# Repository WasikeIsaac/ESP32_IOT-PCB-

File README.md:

# ESP32_IOT-PCB-
ESP32 IoT board: 4-layer KiCad PCB with USB-C, BME280, mic, audio amp, SD card, GPIO breakout. Full custom design from schematic to layout.

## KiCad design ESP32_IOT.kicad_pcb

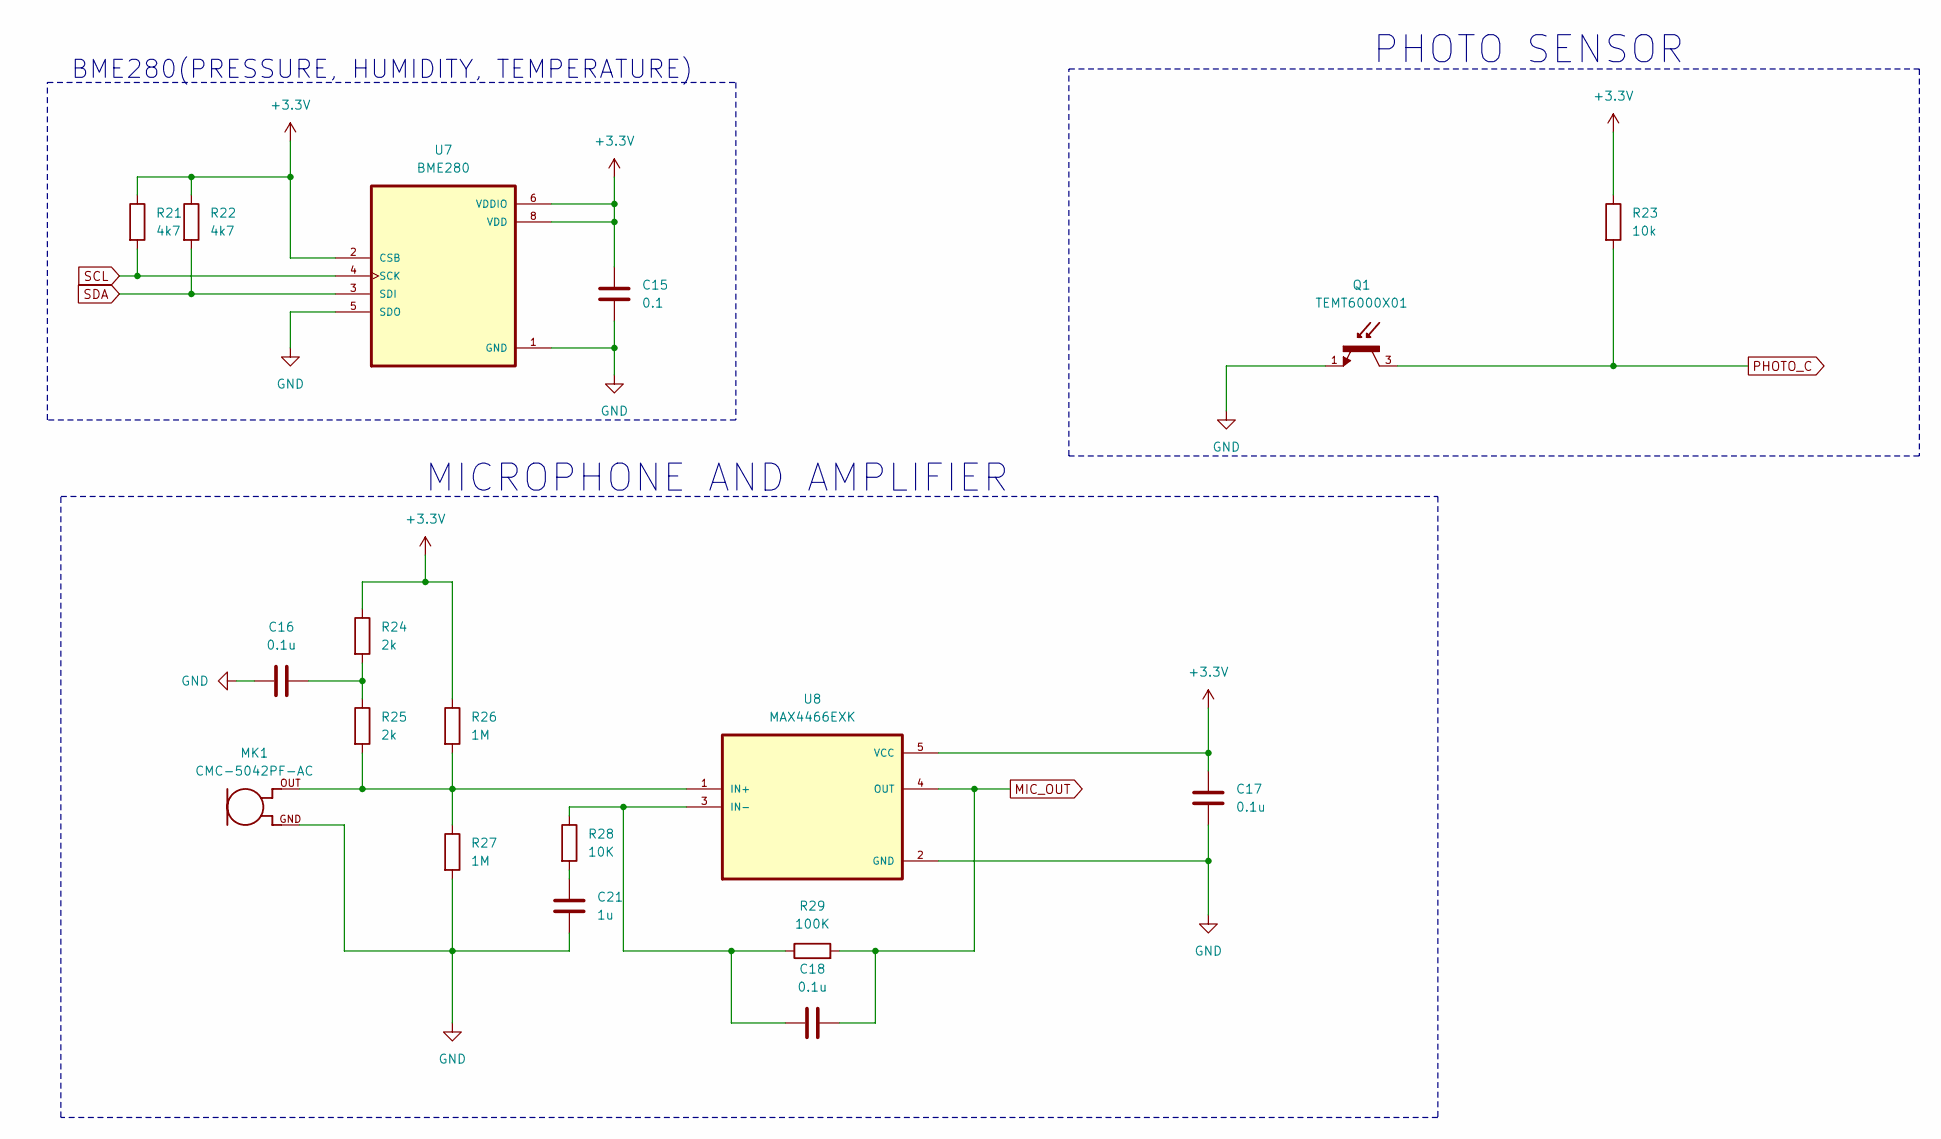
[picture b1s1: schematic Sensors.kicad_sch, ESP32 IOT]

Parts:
C15: 0.1; C_0805_2012Metric
C16, C17, C18: 0.1u; C_0805_2012Metric
C21: 1u; C_0805_2012Metric
MK1: CMC-5042PF-AC; CUI_CMC-5042PF-AC
Q1: TEMT6000X01; TRANS_TEMT6000X01; PARTREV 1.9
R21, R22: 4k7; R_0805_2012Metric
R23: 10k; R_0805_2012Metric
R24, R25: 2k; R_0805_2012Metric
R26, R27: 1M; R_0805_2012Metric
R28: 10K; R_0805_2012Metric
R29: 100K; R_0805_2012Metric
U7: BME280; PSON65P250X250X100-8N
U8: MAX4466EXK; SOT65P210X110-5N

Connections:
+3.3V: C15.1, C17.1, R21.1, R22.1, R23.1, R24.1, R26.1, U7.2 (CSB), U7.6 (VDDIO), U7.8 (VDD), U8.5 (VCC); also elsewhere on the board
GND: C15.2, C16.1, C17.2, C21.1, MK1.GND, Q1.1, R27.2, U7.1 (GND), U7.5 (SDO), U7.7 (GND), U8.2 (GND); also elsewhere on the board
MIC_OUT: C18.2, R29.2, U8.4 (OUT); also elsewhere on the board
unnamed: C16.2, R24.2, R25.1
unnamed: C21.2, R28.2
unnamed: MK1.OUT, R25.2, R26.2, R27.1, U8.1 (IN+)
unnamed: C18.1, R28.1, R29.1, U8.3 (IN-)
PHOTO_C: Q1.3, R23.2; also elsewhere on the board
SCL: R21.2, U7.4 (SCK); also elsewhere on the board
SDA: R22.2, U7.3 (SDI); also elsewhere on the board

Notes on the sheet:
PHOTO SENSOR
BME280(PRESSURE, HUMIDITY, TEMPERATURE)
MICROPHONE AND AMPLIFIER

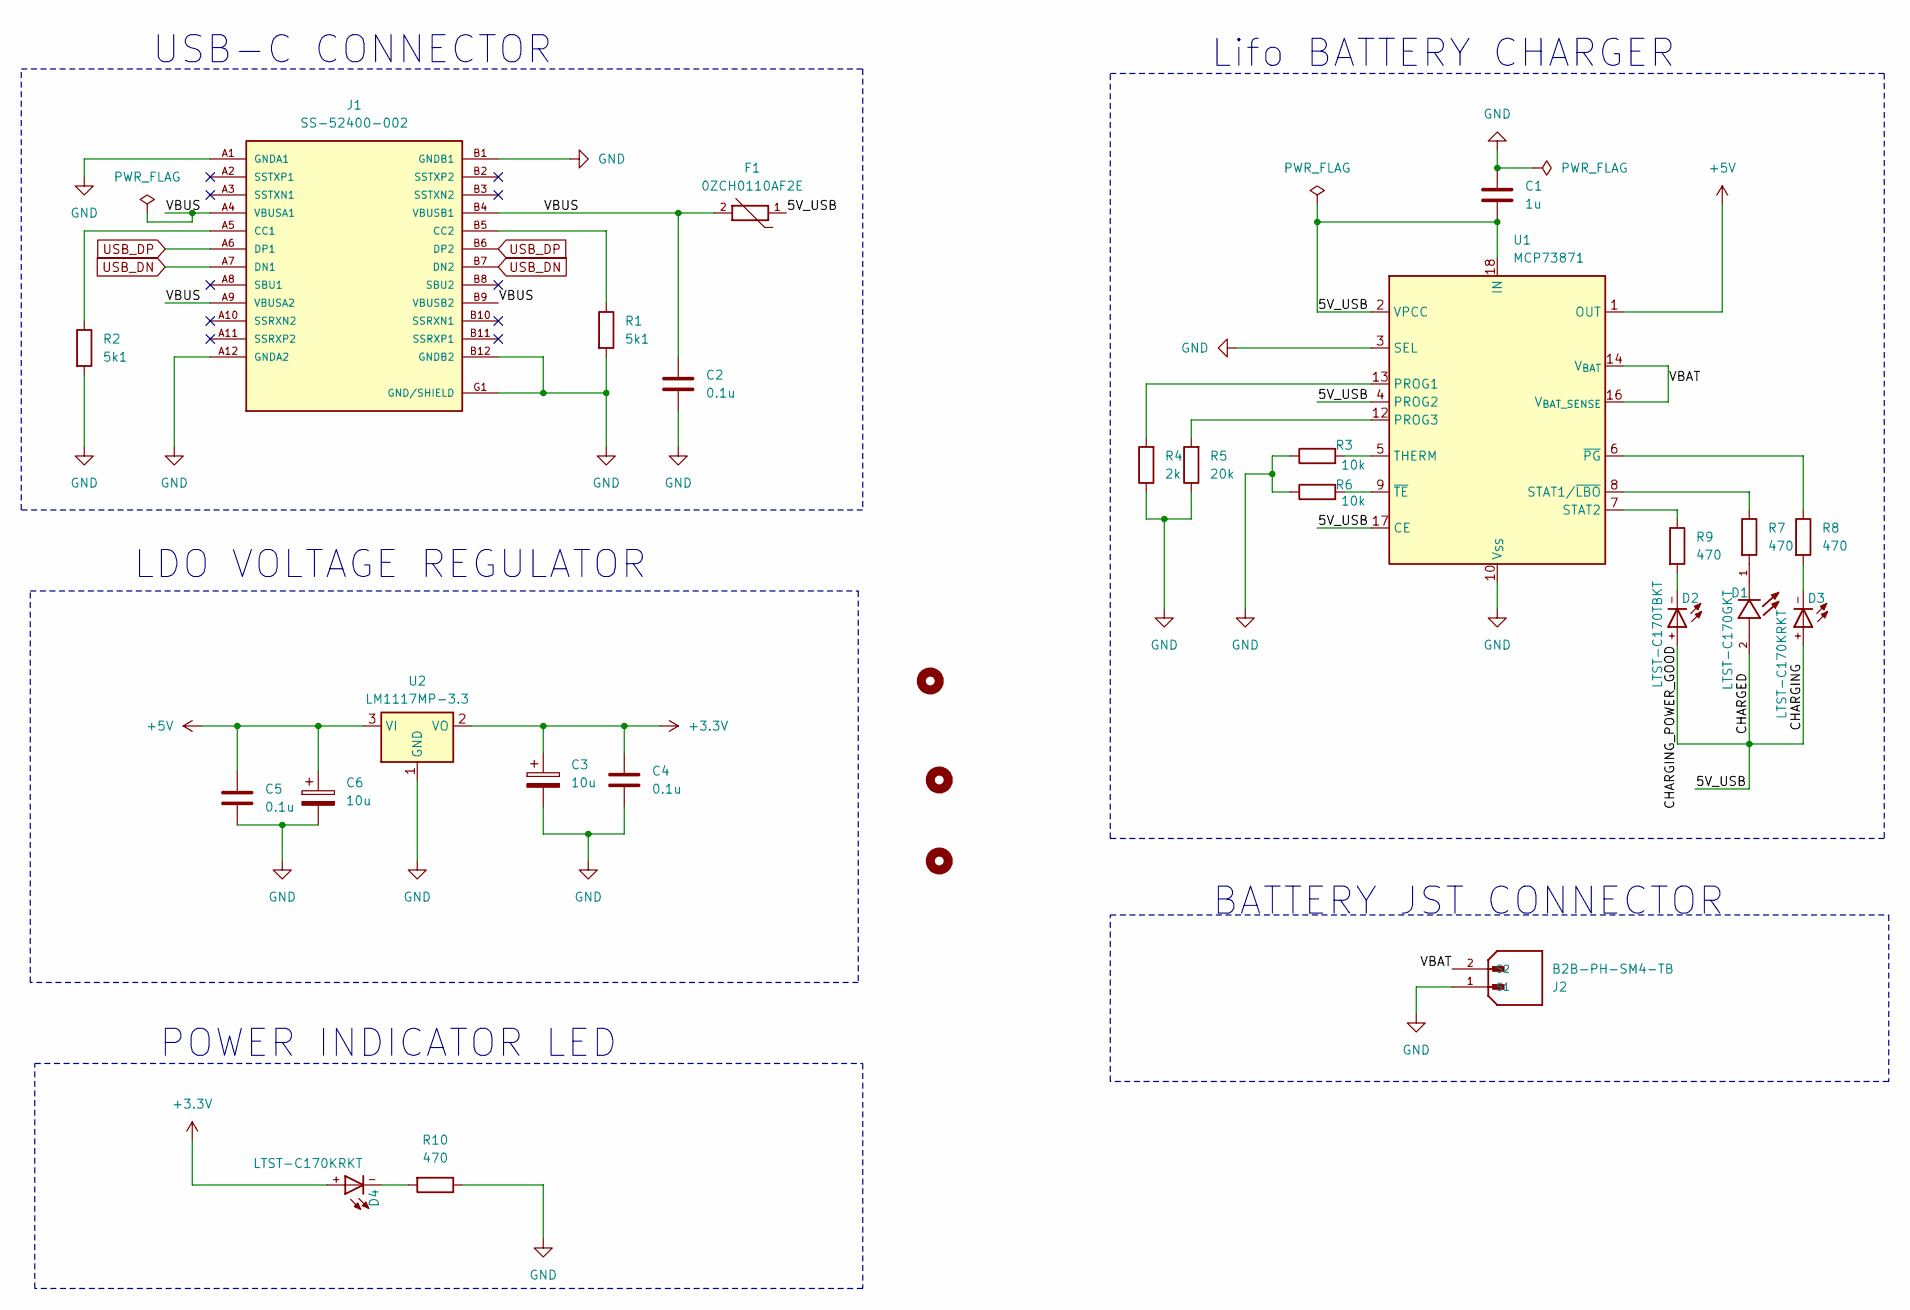
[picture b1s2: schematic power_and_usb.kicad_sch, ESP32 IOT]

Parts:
C1: 1u; C_0805_2012Metric
C2, C4, C5: 0.1u; C_0805_2012Metric
C3, C6: 10u; RESC3216X125N
D1: LTST-C170GKT; LED_LTST-C170GKT; PARTREV I
D2: LTST-C170TBKT; DIOC200X125X110
D3, D4: LTST-C170KRKT; DIOC200X125X110
F1: 0ZCH0110AF2E; FUSC3225X100N; PARTREV Apr2023
H1, H2, H3: MountingHole; MountingHole_2.5mm
J1: SS-52400-002; BELFUSE_SS-52400-002; PARTREV A0
J2: B2B-PH-SM4-TB; JST_B2B-PH-SM4-TB; PARTREV N/A
R1, R2: 5k1; R_0805_2012Metric
R3, R6: 10k; R_0805_2012Metric
R4: 2k; R_0805_2012Metric
R5: 20k; R_0805_2012Metric
R7, R8, R9, R10: 470; R_0805_2012Metric
U1: MCP73871; QFN-20-1EP_4x4mm_P0.5mm_EP2.5x2.5mm
U2: LM1117MP-3.3; SOT-223-3_TabPin2

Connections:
+3.3V: C3.1, C4.1, D4.+, U2.2 (VO); also elsewhere on the board
+5V: C5.1, C6.1, U1.1 (OUT), U1.20 (OUT), U2.3 (VI)
/Power_and USB_Module/5V_USB: C1.2, D1.2, D2.+, D3.+, F1.1, U1.2 (VPCC), U1.4 (PROG2), U1.17 (CE), U1.18 (IN), U1.19 (IN)
/Power_and USB_Module/VBAT: J2.2 (S2), U1.14 (V_{BAT}), U1.15 (V_{BAT}), U1.16 (V_{BAT_SENSE})
/Power_and USB_Module/VBUS: C2.1, F1.2, J1.A4 (VBUSA1), J1.A9 (VBUSA2), J1.B4 (VBUSB1), J1.B9 (VBUSB2)
GND: C1.1, C2.2, C3.2, C4.2, C5.2, C6.2, J1.A1 (GNDA1), J1.A12 (GNDA2), J1.B1 (GNDB1), J1.B12 (GNDB2), J1.G1 (GND/SHIELD), J1.G2 (GND/SHIELD), J1.G3 (GND/SHIELD), J1.G4 (GND/SHIELD), J1.S1 (GND/SHIELD), J1.S2 (GND/SHIELD), J1.S3 (GND/SHIELD), J1.S4 (GND/SHIELD), J2.1 (S1), R1.2, R2.2, R3.1, R4.1, R5.1, R6.1, R10.1, U1.3 (SEL), U1.10 (V_{SS}), U1.11 (V_{SS}), U1.21 (V_{SS}), U2.1 (GND); also elsewhere on the board
unnamed: D1.1, R7.2
unnamed: D2.-, R9.2
unnamed: D3.-, R8.2
unnamed: D4.-, R10.2
unnamed: J1.A5 (CC1), R2.1
unnamed: J1.B5 (CC2), R1.1
unnamed: R4.2, U1.13 (PROG1)
unnamed: R5.2, U1.12 (PROG3)
unnamed: R7.1, U1.8 (STAT1/~LBO)
unnamed: R9.1, U1.7 (STAT2)
unnamed: R3.2, U1.5 (THERM)
unnamed: R8.1, U1.6 (~PG)
unnamed: R6.2, U1.9 (~TE)
USB_DN: J1.A7 (DN1), J1.B7 (DN2); also elsewhere on the board
USB_DP: J1.A6 (DP1), J1.B6 (DP2); also elsewhere on the board

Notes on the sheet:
Lifo BATTERY CHARGER
USB-C CONNECTOR
LDO VOLTAGE REGULATOR
BATTERY JST CONNECTOR
POWER INDICATOR LED

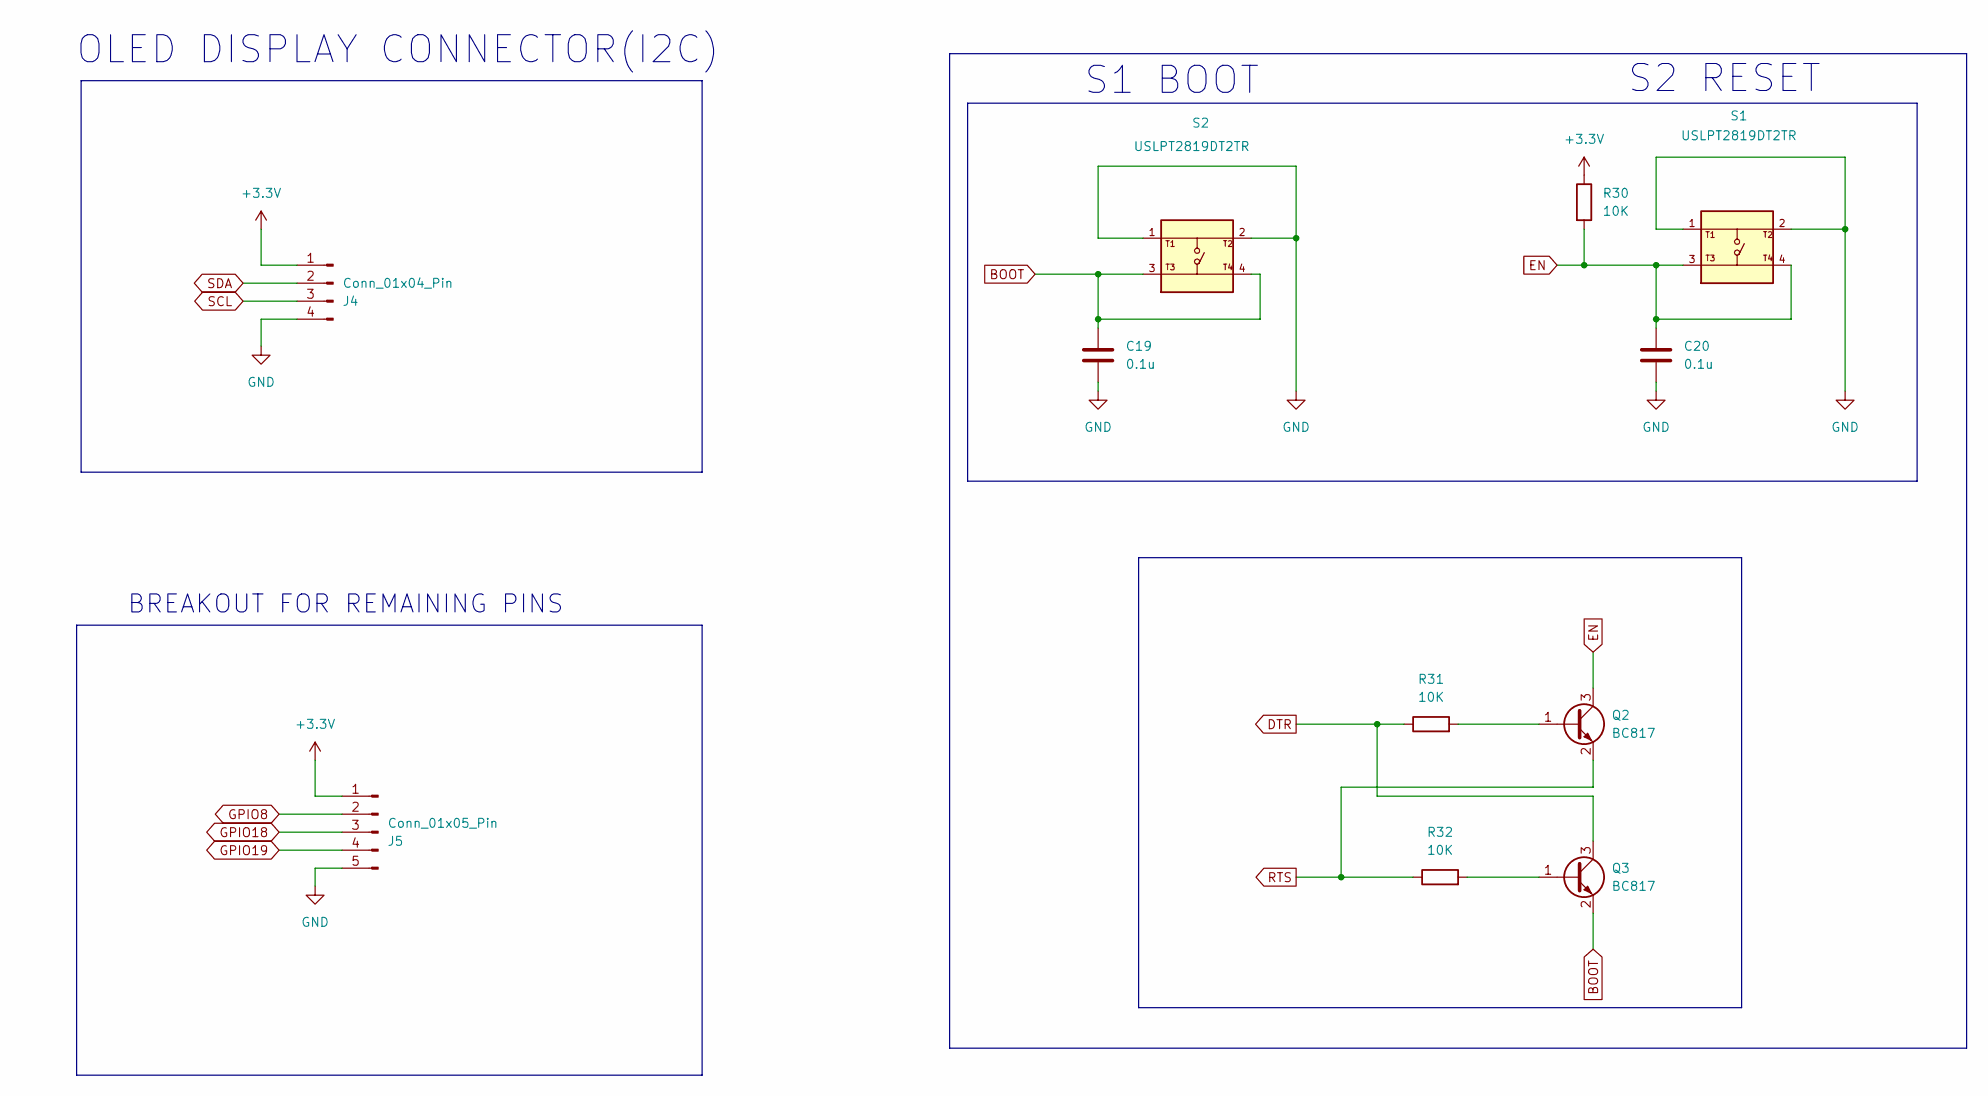
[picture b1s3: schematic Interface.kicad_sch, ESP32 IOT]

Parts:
C19, C20: 0.1u; C_0805_2012Metric
J4: Conn_01x04_Pin; PinHeader_1x04_P2.54mm_Vertical
J5: Conn_01x05_Pin; PinHeader_1x05_P2.54mm_Vertical
Q2, Q3: BC817; SOT-23
R30, R31, R32: 10K; R_0805_2012Metric
S1, S2: USLPT2819DT2TR; SW_USLPT2819DT2TR; PARTREV P

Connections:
+3.3V: J4.1, J5.1, R30.1; also elsewhere on the board
BOOT: C19.1, Q3.2 (E), S2.3, S2.4; also elsewhere on the board
DTR: Q3.3 (C), R31.1; also elsewhere on the board
EN: C20.1, Q2.3 (C), R30.2, S1.3, S1.4; also elsewhere on the board
GND: C19.2, C20.2, J4.4, J5.5, S1.1, S1.2, S2.1, S2.2; also elsewhere on the board
GPIO8: J5.2; also elsewhere on the board
GPIO18: J5.3; also elsewhere on the board
GPIO19: J5.4; also elsewhere on the board
unnamed: Q2.1 (B), R31.2
unnamed: Q3.1 (B), R32.2
RTS: Q2.2 (E), R32.1; also elsewhere on the board
SCL: J4.3; also elsewhere on the board
SDA: J4.2; also elsewhere on the board

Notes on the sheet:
OLED DISPLAY CONNECTOR(I2C)
S2 RESET
BREAKOUT FOR REMAINING PINS
S1 BOOT

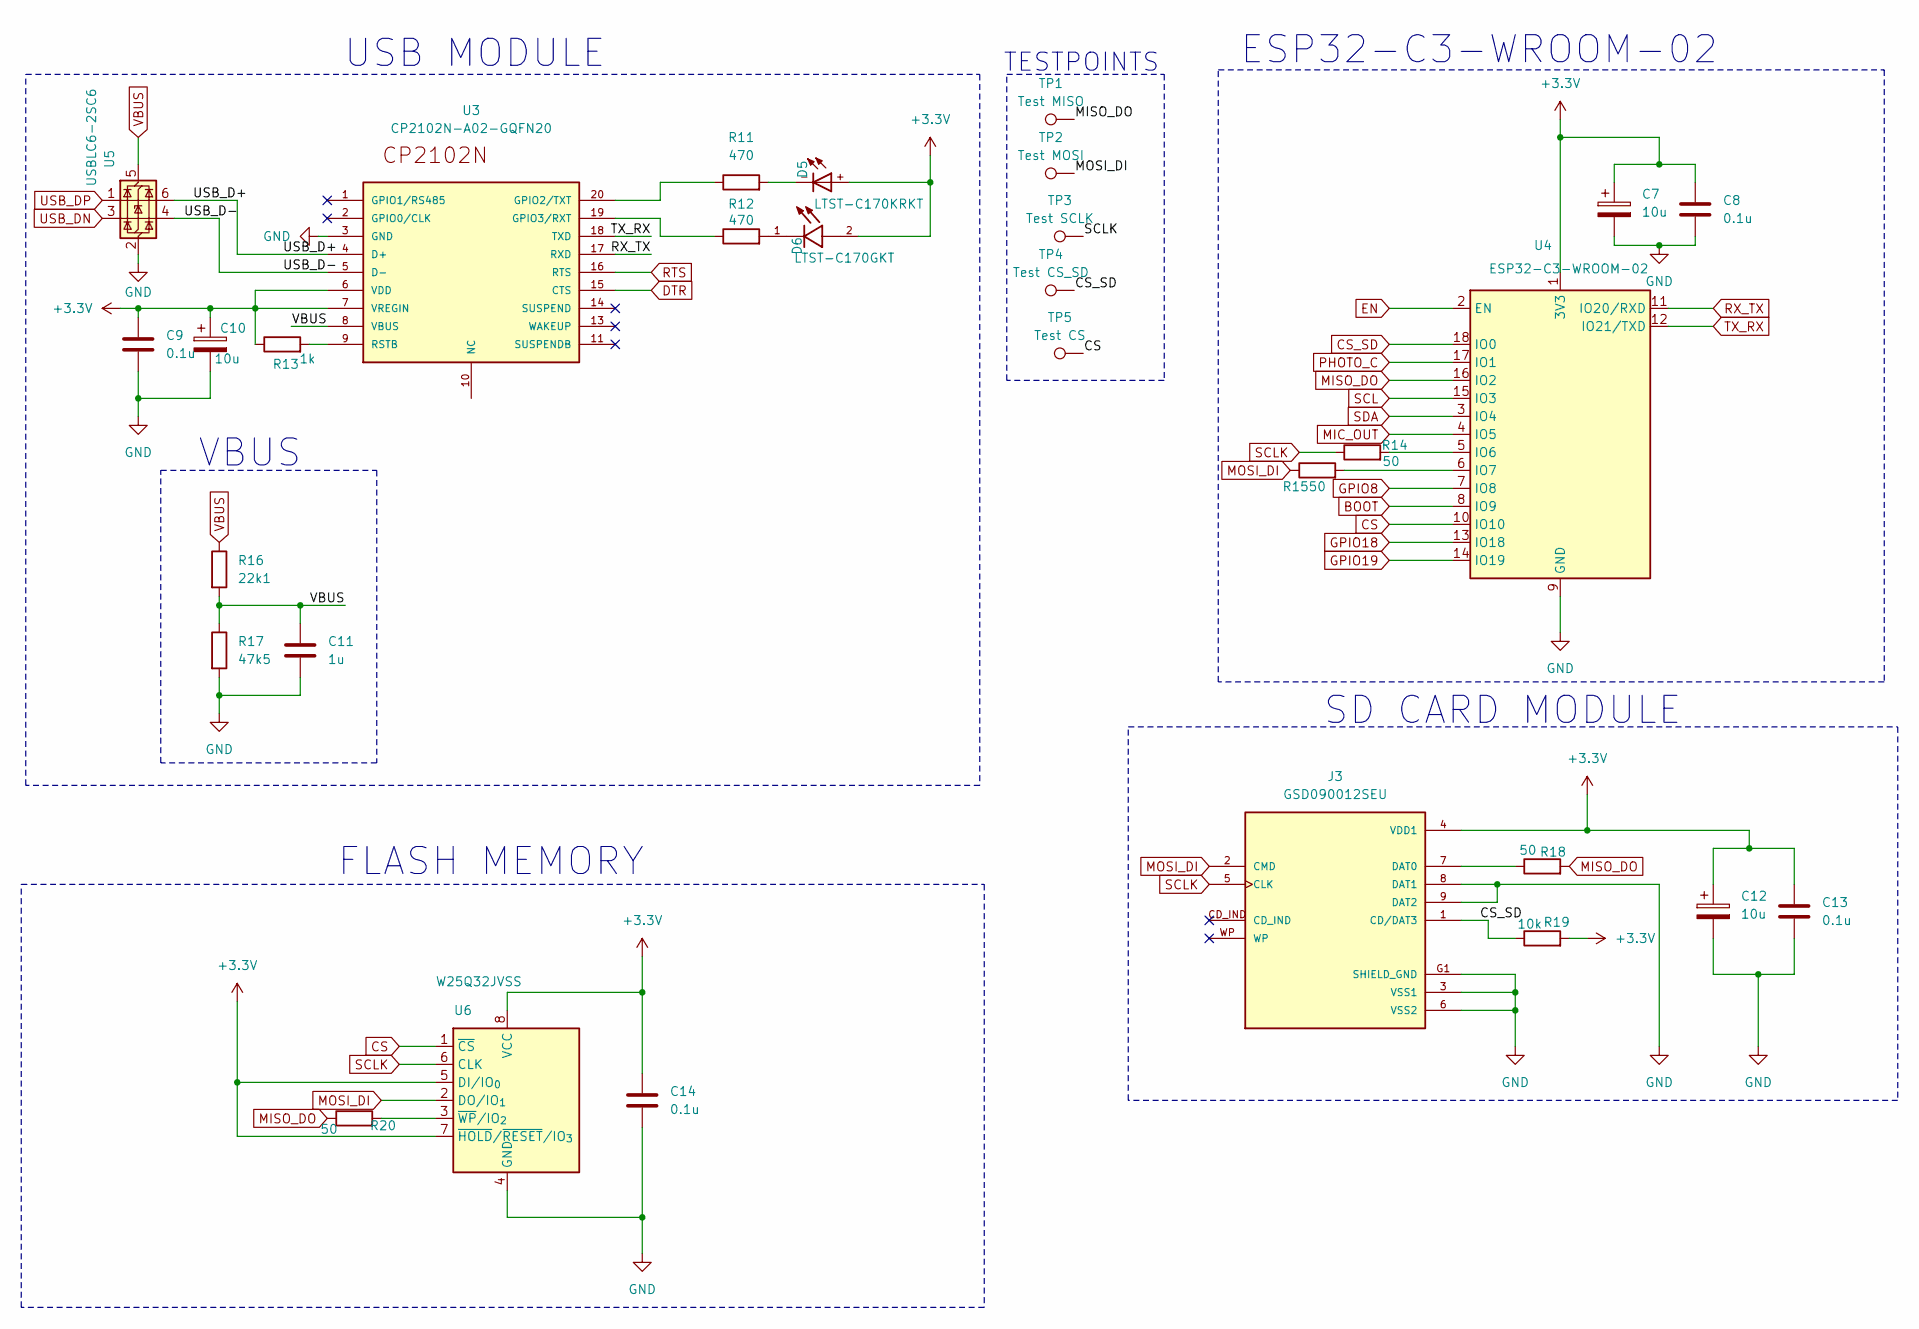
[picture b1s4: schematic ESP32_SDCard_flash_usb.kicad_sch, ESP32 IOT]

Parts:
C7, C10, C12: 10u; RESC3216X125N
C8, C9, C13, C14: 0.1u; C_0805_2012Metric
C11: 1u; C_0805_2012Metric
D5: LTST-C170KRKT; DIOC200X125X110
D6: LTST-C170GKT; LED_LTST-C170GKT; PARTREV I
J3: GSD090012SEU; AMPHENOL_GSD090012SEU; PARTREV E
R11, R12: 470; R_0805_2012Metric
R13: 1k; R_0805_2012Metric
R14, R15, R18, R20: 50; R_0805_2012Metric
R16: 22k1; R_0805_2012Metric
R17: 47k5; R_0805_2012Metric
R19: 10k; R_0805_2012Metric
TP1: Test MISO; TestPoint_Pad_D1.0mm
TP2: Test MOSI; TestPoint_Pad_D1.0mm
TP3: Test SCLK; TestPoint_Pad_D1.0mm
TP4: Test CS_SD; TestPoint_Pad_D1.0mm
TP5: Test CS; TestPoint_Pad_D1.0mm
U3: CP2102N-A02-GQFN20; WFQFN-20
U4: ESP32-C3-WROOM-02
U5: USBLC6-2SC6; SOT-23-6
U6: W25Q32JVSS; SOIC-8_5.3x5.3mm_P1.27mm

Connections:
+3.3V: C7.1, C8.1, C9.1, C10.1, C12.1, C13.1, C14.1, D5.+, D6.2, J3.4 (VDD1), R13.1, R19.2, U3.6 (VDD), U3.7 (VREGIN), U4.1 (3V3), U6.5 (DI/IO_{0}), U6.7 (~HOLD/~RESET/IO_{3}), U6.8 (VCC); also elsewhere on the board
/ESP32_SDCard_FlashMemory_USBModule/USB_D+: U3.4 (D+), U5.6 (I/O1)
/ESP32_SDCard_FlashMemory_USBModule/USB_D-: U3.5 (D-), U5.4 (I/O2)
BOOT: U4.8 (IO9); also elsewhere on the board
CS: TP5.1, U4.10 (IO10), U6.1 (~CS)
CS_SD: J3.1 (CD/DAT3), R19.1, TP4.1, U4.18 (IO0)
DTR: U3.15 (CTS); also elsewhere on the board
EN: U4.2 (EN); also elsewhere on the board
GND: C7.2, C8.2, C9.2, C10.2, C11.2, C12.2, C13.2, C14.2, J3.3 (VSS1), J3.6 (VSS2), J3.8 (DAT1), J3.9 (DAT2), J3.G1 (SHIELD_GND), J3.G2 (SHIELD_GND), J3.G3 (SHIELD_GND), J3.G4 (SHIELD_GND), R17.2, U3.3 (GND), U3.12 (GND), U3.EXP (GND), U4.9 (GND), U4.19 (GND), U5.2 (GND), U6.4 (GND); also elsewhere on the board
GPIO8: U4.7 (IO8); also elsewhere on the board
GPIO18: U4.13 (IO18); also elsewhere on the board
GPIO19: U4.14 (IO19); also elsewhere on the board
MIC_OUT: U4.4 (IO5); also elsewhere on the board
MISO_DO: R18.2, R20.1, TP1.1, U4.16 (IO2)
MOSI_DI: J3.2 (CMD), R15.1, TP2.1, U6.2 (DO/IO_{1})
unnamed: D5.-, R11.2
unnamed: D6.1, R12.2
unnamed: J3.7 (DAT0), R18.1
unnamed: R11.1, U3.20 (GPIO2/TXT)
unnamed: R12.1, U3.19 (GPIO3/RXT)
unnamed: R13.2, U3.9 (RSTB)
unnamed: R14.2, U4.5 (IO6)
unnamed: R15.2, U4.6 (IO7)
unnamed: R20.2, U6.3 (~WP/IO_{2})
PHOTO_C: U4.17 (IO1); also elsewhere on the board
RTS: U3.16 (RTS); also elsewhere on the board
RX_TX: U3.17 (RXD), U4.11 (IO20/RXD)
SCL: U4.15 (IO3); also elsewhere on the board
SCLK: J3.5 (CLK), R14.1, TP3.1, U6.6 (CLK)
SDA: U4.3 (IO4); also elsewhere on the board
TX_RX: U3.18 (TXD), U4.12 (IO21/TXD)
USB_DN: U5.3 (I/O2); also elsewhere on the board
USB_DP: U5.1 (I/O1); also elsewhere on the board
VBUS: C11.1, R16.1, R16.2, R17.1, U3.8 (VBUS), U5.5 (VBUS)

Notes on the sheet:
ESP32-C3-WROOM-02
SD CARD MODULE
FLASH MEMORY
TESTPOINTS
VBUS
USB MODULE

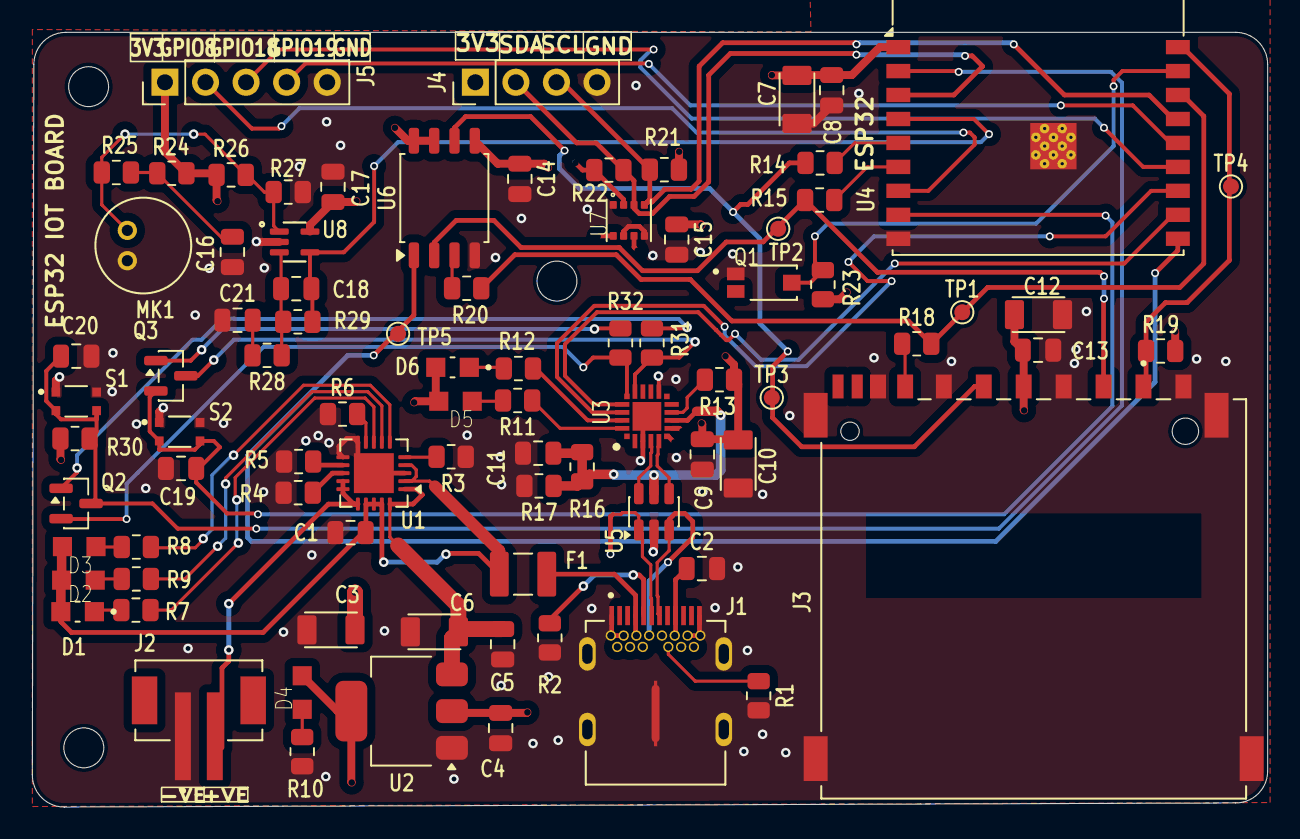
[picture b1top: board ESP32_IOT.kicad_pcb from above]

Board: 4 copper layers, 77.3 x 48.5 mm, 87 parts (0 on the bottom side), 57 nets.
